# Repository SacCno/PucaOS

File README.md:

# PucaOS

### **This project is in development. There are safeguards and failsafes that are yet to be implemented! It should not be used to manage a terrarium in its current state!**

PucaOS is an embedded system written for the Arduino Nano ESP32. It includes an accompanying Android app, which allows for remote interfacing with the Arduino.
The Arduino takes in measurements from DS18B20 temperature probes and compares them against a saved schedule. Based on these measurements and the configured schedule, the Arduino controls a Tasmota smart plug over the local network using HTTP commands to regulate the terrarium's temperature.

## Images

<table align="center">
  <tr>
    <td>
      
      <br><br>
      
    </td>
    <td>
      
    </td>
  </tr>
</table>

<table align="center">
  <tr>
    <td>
      
    </td>
    <td>
      
      <br><br>
      
    </td>
  </tr>
</table>

## Features

* Temperature reading.
* Create and set custom schedules with:
  1. Custom starting times.
  2. Custom set temperatures.
* Manually control the lamp with manual control mode.

## Dependencies

* Mongoose
* DallasTemperature
* OneWire
* Wire
* Adafruit_SSD1306
* Adafruit_GFX

## Technologies
* Arduino
* DS18B20
* WiFi
* MQTT
* HTTP
* C/C++
* Kotlin/Java

## Included

1. The source code for the Arduino program.
2. The source code for the Android app.
3. The gerbers and KiCad project files for the PCB.
4. The .STEP files for the housing and Stevenson Screen.

## Implementation

Clone the repository and setup *'config.h'*

```bash
git clone https://github.com/SacCno/PucaOS && cd PucaOS/PucaOS-Arduino && cp config.example.h config.h && cp ../PucaOS-Android/local.example.properties ../PucaOS-Android/local.properties
```

On Powershell you may have to use this command instead.

```bash
git clone https://github.com/SacCno/PucaOS; if ($LASTEXITCODE -eq 0) { Copy-Item PucaOS/PucaOS-Arduino/config.example.h PucaOS/PucaOS-Arduino/config.h; Copy-Item PucaOS/PucaOS-Android/local.example.properties PucaOS/PucaOS-Android/local.properties }
```

### Arduino

The above command will have copied *'config.example.h'* into *'PucaOS-Arduino/'* as *'config.h'*.
This file will be ignored by git so you can safely fill in your details and push commits without sharing your WiFi password! **The program will not run if the values in the new *'config.h'* are not filled in accurately.**

*To connect to your MQTT broker you will need to find their TLS CA certificate and include it in your config.h file. The example file contains the CA cert for HiveMQ Cloud, if you are using a different broker you will need to change the cert.*

To compile and upload the program onto your Arduino Nano ESP32:

1. Ensure all files are in the same directory as *'PucaOS-Arduino.ino'*
2. Open Arduino IDE
3. Click *'File -> Open...'*
4. Select *'PucaOS-Arduino.ino'*
5. Ensure Arduino Nano ESP32 is connected to the computer and that the appropriate board and port are selected in 'tools'
6. Go to *'Tools -> Pin Numbering'* and ensure it is set to *'GPIO'*
7. Click *'Upload Sketch'*

### Android

In Android Studio, open the *PucaOS-Android/* folder as a project, and let the gradle build.

Open *'local.properties,'* which should've been copied into PucaOS-Android with the above command, and fill in your values. This file will also be ignored by Git, so your information is safe.

## License

MIT License - See [LICENSE](LICENSE).

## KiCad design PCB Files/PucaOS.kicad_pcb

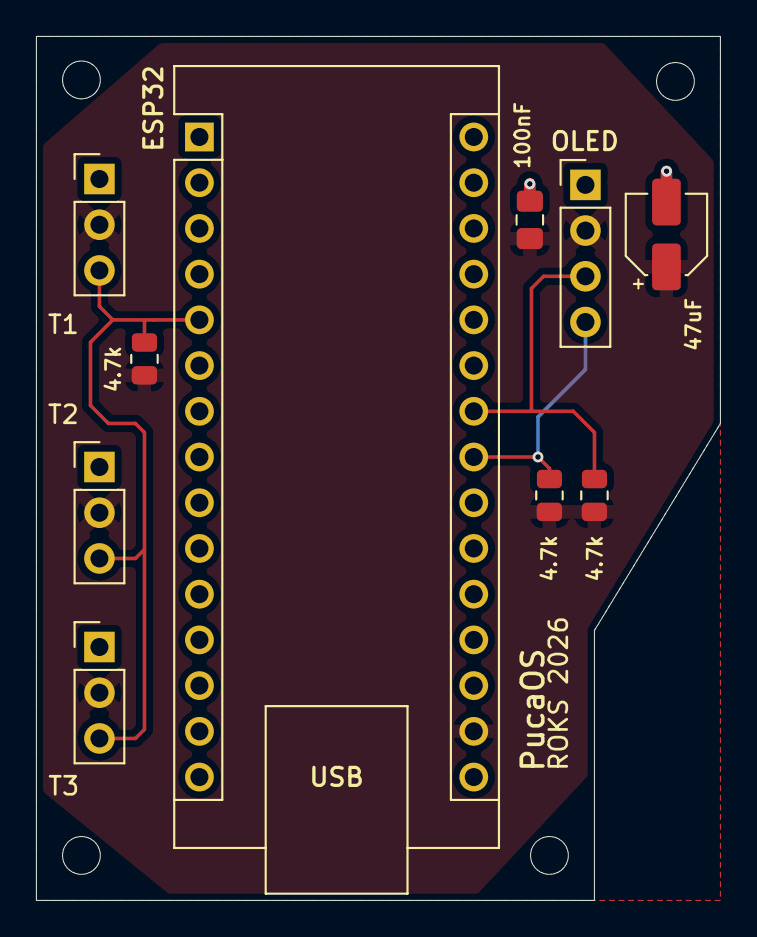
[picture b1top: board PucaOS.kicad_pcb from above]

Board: 2 copper layers, 38.0 x 48.0 mm, 8 parts (0 on the bottom side), 5 nets.

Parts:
4.7k, 4.7k#2, 4.7k#3: 4.7k; R_0805_2012Metric
ESP32: Arduino_Nano_ESP32; Arduino_Nano
OLED: DISPLAY_OLED; PinHeader_1x04_P2.54mm_Vertical
T1, T2, T3: DS18B20; PinHeader_1x03_P2.54mm_Vertical

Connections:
+3.3V: 4.7k.1, 4.7k#2.2, 4.7k#3.1, ESP32.17 (3V3), OLED.2 (VCC), T1.2, T2.2, T3.2
/A4: 4.7k#3.2, ESP32.23 (SDA/A4), OLED.4 (SDA)
/A5: 4.7k#2.1, ESP32.24 (SCL/A5), OLED.3 (SCL)
/DS18B20 Data: 4.7k.2, ESP32.5 (D2), T1.3, T2.3, T3.3
GND: ESP32.4 (GND), ESP32.29 (GND), OLED.1 (GND), T1.1, T2.1, T3.1
